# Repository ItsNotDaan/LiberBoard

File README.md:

# LiberBoard Electronics Learning Platform

## Vision

Our vision is to bridge the gap in electronics learning and project creation by providing well-documented and easy-to-access information points. We aim to empower individuals and educational institutions with the necessary tools and resources to ignite creativity and facilitate a seamless learning experience.

## Development

LiberBoard Electronics Learning Platform is developed with the user in mind, ensuring a high degree of modularity and flexibility. The platform consists of two main LiBo PCBs and several add-on boards, each serving a unique purpose and adding a different dimension to the learning process.

### Main Boards

1. **LiBo DUO**: A budget-friendly, two-layer PCB with hand-solderable components.
2. **LiBo QUAD**: A medium-budget, four-layer PCB solderable using a heat plate or oven.
3. **LiBo ESP32-S3 SOM**: A high speed system on module that can be connected to multiple add-on boards.

### Add-on Boards

1. **LiBo StarterBoard**: A board featuring a 16x2 LCD, 16 bit LEDs, an ADC sensor, and a temperature sensor.
2. **LiBo ArduinoBoard**: A board with an Arduino pinout, capable of communicating with Arduino Modules.
3. **LiBo DSPBoard**: An audio processing board with components for audio input/output, microphone, and speaker connectors.
4. **LiBo BaseBoard**: A programming stand/main board base station with easy access pinouts, BNC connectors, and status LEDs.

Each board is accompanied by exercises and code snippets to enable hands-on learning and practical understanding of electronics.

## Used Software and Products

All the LiBo PCB designs are created using the EDA software KiCad. The design files are open source and are available on GitHub, allowing users to recreate, modify, and order the PCBs. The platform also provides options for DIY PCB creation or ordering from the site.

## Conclusion

LiberBoard Electronics Learning Platform is a comprehensive solution for anyone looking to delve into the world of electronics. By providing well-documented, easy-to-use, and flexible resources, we hope to inspire a new generation of electronics enthusiasts and professionals.

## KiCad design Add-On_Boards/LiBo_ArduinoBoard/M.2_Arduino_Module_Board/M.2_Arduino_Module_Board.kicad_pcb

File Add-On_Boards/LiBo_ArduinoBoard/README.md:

# LiBo ArduinoBoard

The LiBo ArduinoBoard is an add-on board with Arduino pinout, enabling communication with Arduino modules.

## Features

- Arduino pinout
- M.2 interface
- Maximum component size: 0805
- Able to communicate with Arduino Modules
- Able to program main board using this board

## Exercises

- Blink
- SPI

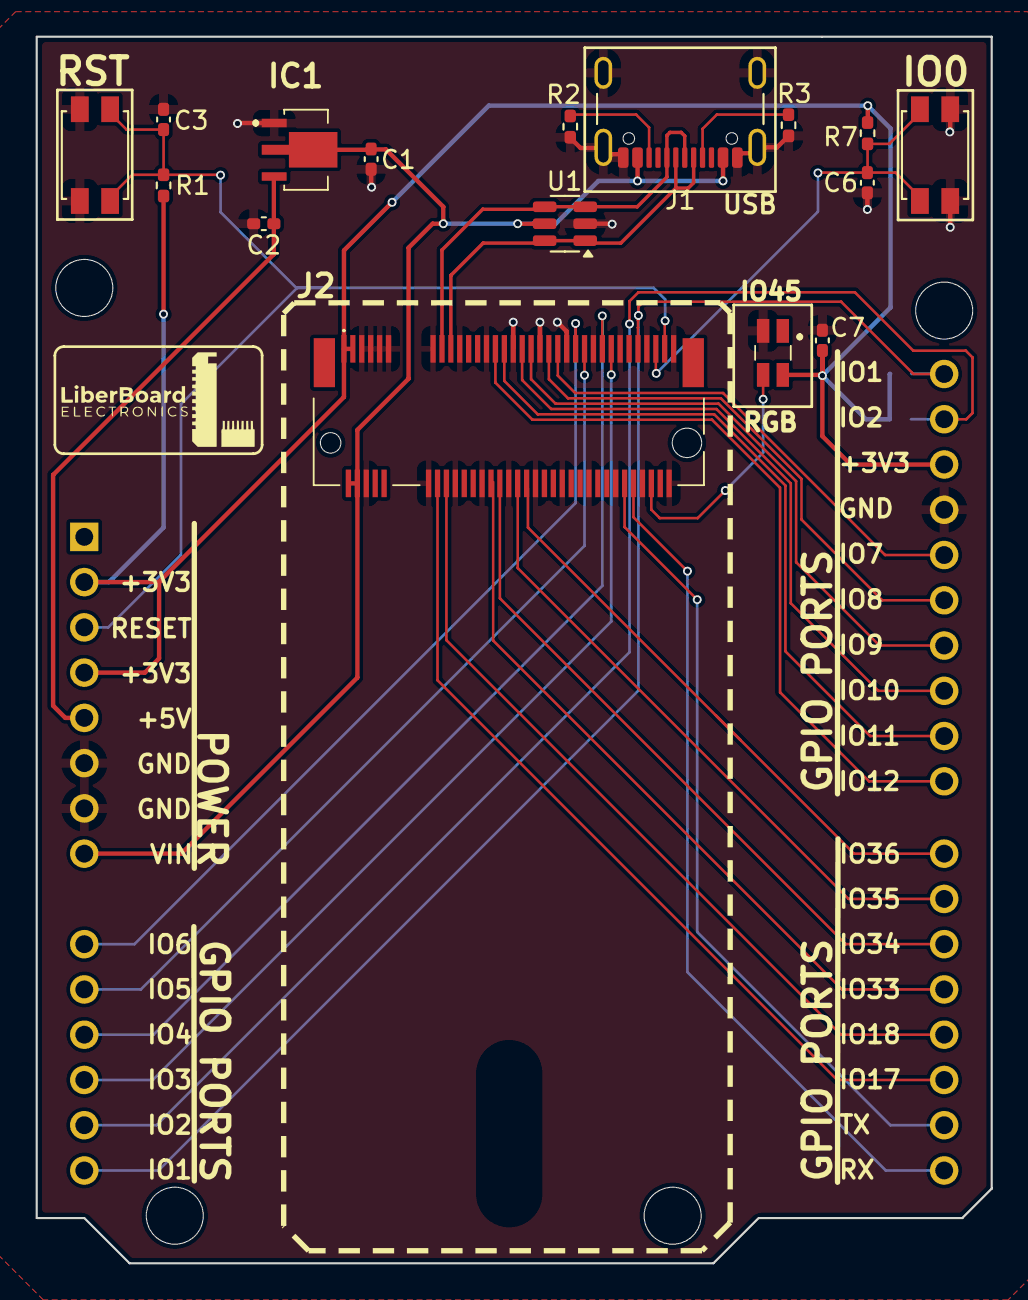
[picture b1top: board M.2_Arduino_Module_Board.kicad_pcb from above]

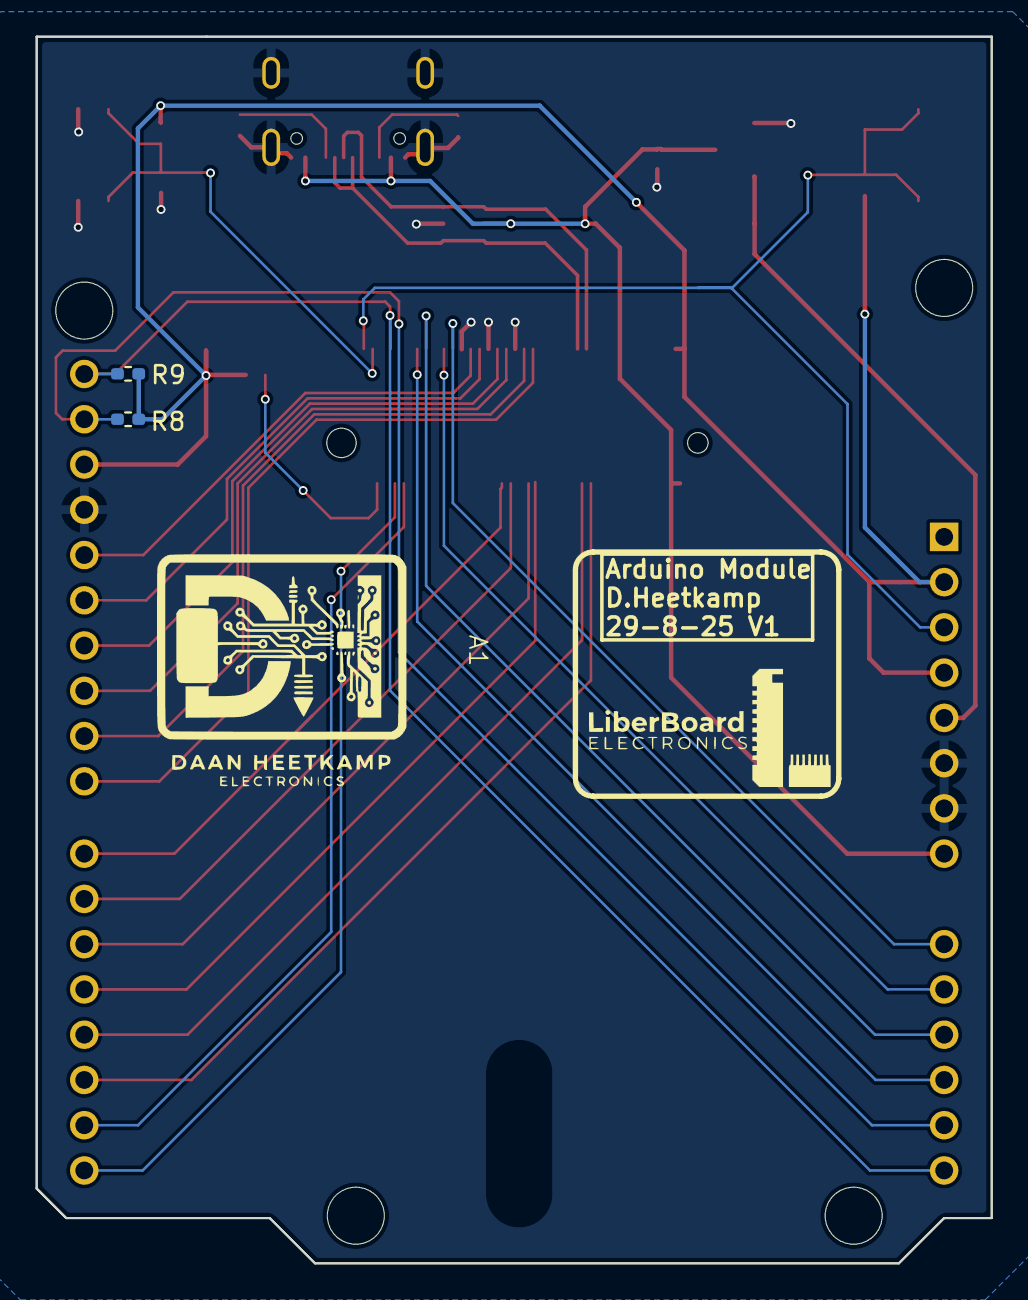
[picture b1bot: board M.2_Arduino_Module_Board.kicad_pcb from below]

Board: 2 copper layers, 53.6 x 68.8 mm, 19 parts (3 on the bottom side), 31 nets.

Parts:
A1: Arduino_Uno_Footprint
BOOT1: SW_BOOT; SW_SPST_EVQP2
C1, C2: 1u; C_0402_1005Metric_Pad0.74x0.62mm_HandSolder
C3, C6, C7: 100n; C_0402_1005Metric_Pad0.74x0.62mm_HandSolder
IC1: MCP1702T-5002E_MB; MCP1703T5002EMB
J1: USB_C_Receptacle_USB2.0; USB_C_Receptacle_GCT_USB4105-xx-A_16P_TopMnt_Horizontal
J2: 2199230-3; 21992303
LED1: WS2812C-2020; WS2812C2020
R1, R7: 10k; R_0402_1005Metric_Pad0.72x0.64mm_HandSolder
R2, R3, R8, R9: 5k1; R_0402_1005Metric_Pad0.72x0.64mm_HandSolder
RST1: SW_RST; SW_SPST_EVQP2
U1: USBLC6-2SC6; SOT-23-6

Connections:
+3V3: A1.2 (IOREF), A1.4 (3V3), A1.30 (AREF), C7.1, J2.1, J2.3, LED1.4 (VDD), R1.1, R7.1, R8.1, R9.1
+5V: A1.5 (+5V), C2.1, IC1.3 (VOUT)
/CHIP_BOOT: BOOT1.2, C6.1, J2.71, R7.2
/CHIP_PU: A1.3 (~RESET), C3.1, J2.73, R1.2, RST1.2
/GPIO1: A1.14 (SCL/A5), A1.32 (SCL/A5), J2.67, R9.2
/GPIO2: A1.13 (SDA/A4), A1.31 (SDA/A4), J2.65, R8.2
/GPIO3: A1.12 (A3), J2.61
/GPIO4: A1.11 (A2), J2.59
/GPIO5: A1.10 (A1), J2.55
/GPIO6: A1.9 (A0), J2.53
/GPIO7: A1.28 (D13), J2.49
/GPIO8: A1.27 (D12), J2.47
/GPIO9: A1.26 (D11), J2.43
/GPIO10: A1.25 (D10), J2.41
/GPIO11: A1.24 (D9), J2.37
/GPIO12: A1.23 (D8), J2.35
/GPIO17: A1.17 (D2), J2.22
/GPIO18: A1.18 (D3), J2.24
/GPIO33: A1.19 (D4), J2.34
/GPIO34: A1.20 (D5), J2.36
/GPIO35: A1.21 (D6), J2.40
/GPIO36: A1.22 (D7), J2.42
/GPIO45: J2.70, LED1.3 (DI)
/U0RXD: A1.15 (D0/RX), J2.66
/U0TXD: A1.16 (D1/TX), J2.64
/USB_CC1: J1.A5 (CC1), R3.1
/USB_CC2: J1.B5 (CC2), R2.1
/USB_D+: J1.A6 (D+), J1.B6 (D+), J2.23, U1.3 (I/O2), U1.4 (I/O2)
/USB_D-: J1.A7 (D-), J1.B7 (D-), J2.25, U1.1 (I/O1), U1.6 (I/O1)
Earth: A1.6 (GND), A1.7 (GND), A1.29 (GND), BOOT1.1, C1.2, C2.2, C3.2, C6.2, C7.2, IC1.1 (GND), J1.A1 (GND), J1.A12 (GND), J1.B1 (GND), J1.B12 (GND), J1.S1 (SHIELD), J2.5, J2.6, J2.7, J2.9, J2.11, J2.20, J2.21, J2.26, J2.27, J2.32, J2.33, J2.38, J2.39, J2.44, J2.45, J2.50, J2.51, J2.56, J2.57, J2.62, J2.63, J2.68, J2.69, J2.74, J2.75, LED1.2 (GND), R2.2, R3.2, RST1.1, U1.2 (GND)
VBUS: A1.8 (VIN), C1.1, IC1.2 (VIN_1), IC1.4 (VIN_2), J1.A4 (VBUS), J1.A9 (VBUS), J1.B4 (VBUS), J1.B9 (VBUS), J2.2, J2.4, U1.5 (VBUS)

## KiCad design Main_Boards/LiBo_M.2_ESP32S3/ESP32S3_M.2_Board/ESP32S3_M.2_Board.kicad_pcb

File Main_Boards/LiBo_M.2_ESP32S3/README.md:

## ESP32-S3, M.2 based System on Module (SOM)

This is my first KiCad project, developed over the last 2 months alongside my EPS project and work. 

## Versions:
### V1
The first version that was created. Soldered by hand. Did not boot properly. 

### V2
The second version got a redesign of the main ESP32 S3 connections. This time hopefully with the correct connections. 
Some bootpins were removed to change to a more usable setup. The board has also been ordered with assembly to make sure the soldering is correct. 

### Main Components

- **CPU:** ESP32-S3R8
- **Flash:** W25Q16JVUXIQ (16MBIT)
- **Crystals:** 40MHz and 32.768KHz (HSE/LSE)
- **Power/Flashing/Debugging:** USB-C
- **Buck Converter:** TLV62568DBV
- **Buttons:** Two buttons for RESET and BOOT
- **Antenna:** Antenna with PI filter
- **PCB:** 4-layer PCB (Top, GND, VCC, Bottom), internal planes are hidden

All these components are included on a M.2-B-Key footprint. 

## JLCPCB Ordering Details

- **Base Material:** FR-4
- **Layers:** 4
- **Dimension:** 70.97 mm × 70 mm
- **PCB Thickness:** 0.8 mm
- **Specify Stackup:** yes — JLC04081H-7628
- **Impedance Control:** No requirement
- **Material Type:** FR4 TG135
- **Via Covering:** Plugged
- **Surface Finish:** ENIG — Gold Thickness: 1U"
- **Outer Copper Weight:** 1 oz
- **Inner Copper Weight:** 0.5 oz
- **Gold Fingers:** Yes
- **Beveling:** 45°
- **Mark on PCB:** 2D barcode (Serial Number)
- **Min via hole size/diameter:** 0.3 mm / (0.4 / 0.45 mm)
- **Appearance Quality:** IPC Class 2 Standard
- **Silkscreen Technology:** Ink-jet/Screen Printing Silkscreen
- **Package Box:** With JLCPCB logo
- **Board Outline Tolerance:** ±0.2 mm (Regular)

### Notes
- **Layer Sequence:** Top / GND / VCC / Bottom (from design)
- **NOTE:** If a detail is not shown it means the standard is used. 
 
### Inspiration

The idea originated from a desire to create a more complex and smaller PCB that incorporates an expensive CPU. This CPU should be versatile enough to be used on different projects. After watching a video from Phil's Lab, I learned that M.2 was a great alternative to the mostly used header pin setup. 

### Future Plans

The ESP32-S3 is not high-end or anything special, but I plan to quickly redesign this board using the newly announced ESP32-P4. It is a really interesting and high-speed CPU based on the RISC-V architecture and I'm excited to start creating some (DSP) code with it. 

I have ordered the components and the PCB to start experimenting with it.

https://www.linkedin.com/in/daan-heetkamp/

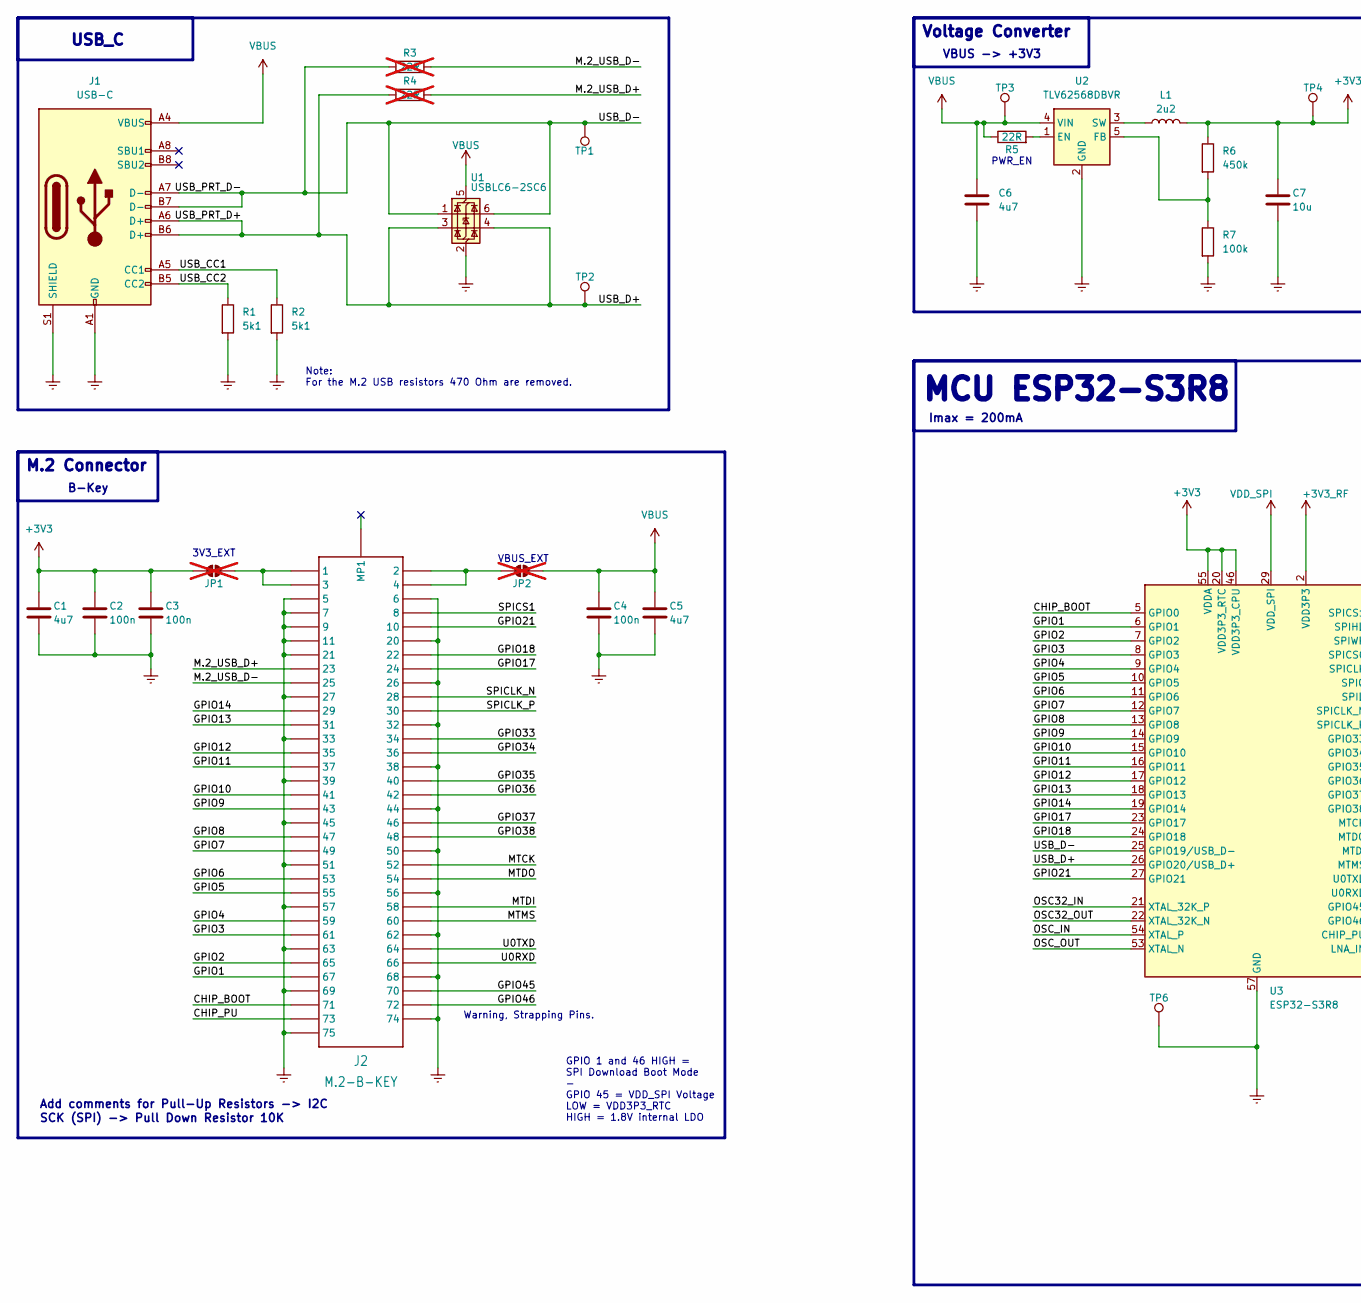
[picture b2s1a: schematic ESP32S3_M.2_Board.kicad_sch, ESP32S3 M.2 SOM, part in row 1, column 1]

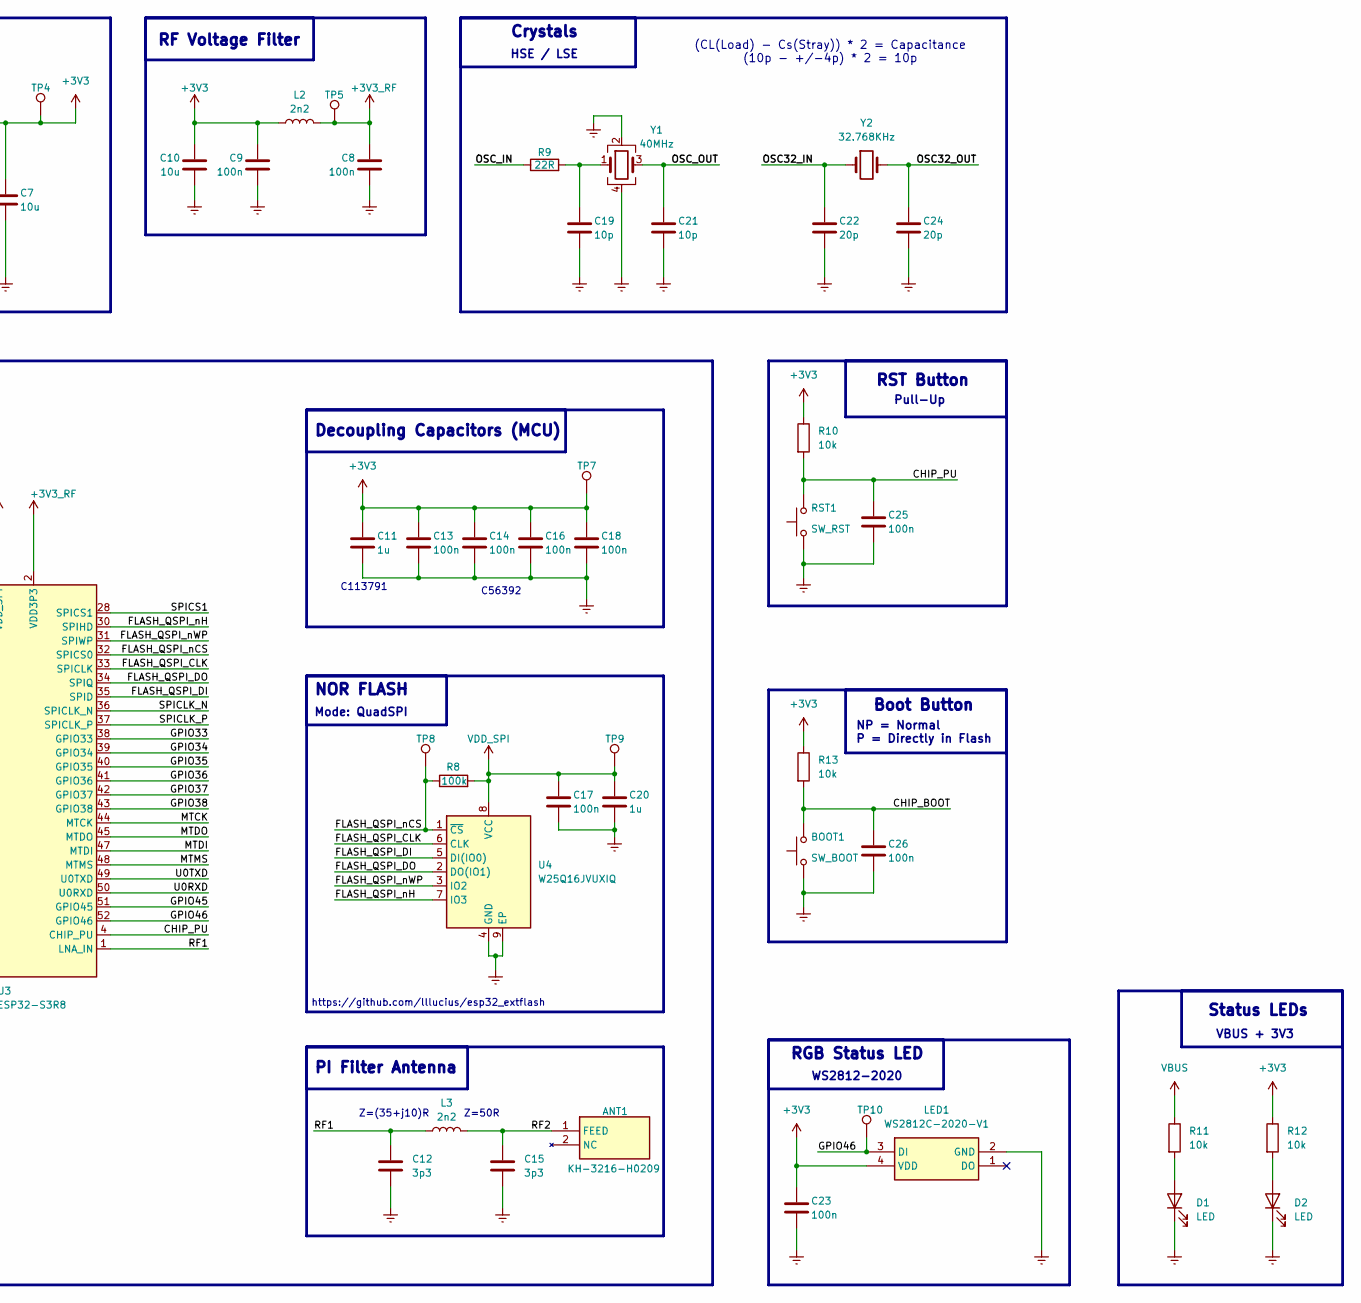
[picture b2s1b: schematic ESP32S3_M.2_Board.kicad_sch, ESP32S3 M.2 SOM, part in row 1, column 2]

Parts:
ANT1: KH-3216-H0209; ANTC3216X140N; Manufacturer_Part_Number KH-3216-H0209; LCSC PART # C2925417
BOOT1: SW_BOOT; SW_SPST_EVQP2; Manufacturer_Part_Number EVQP2P02W; LCSC PART # C512395
C1, C5, C6: 4u7; C_0402_1005Metric_Pad0.74x0.62mm_HandSolder; Manufacturer_Part_Number GRM155R60J475ME47D; LCSC PART # C82453
C2, C3, C4, C8, C9, C13, C14, C16, C17, C18, C23, C25, C26: 100n; C_0402_1005Metric_Pad0.74x0.62mm_HandSolder; Manufacturer_Part_Number C1005X5R1E104KT000E; LCSC PART # C361203
C7, C10: 10u; C_0402_1005Metric_Pad0.74x0.62mm_HandSolder; Manufacturer_Part_Number 0402X106M100CT; LCSC PART # C2992625
C11, C20: 1u; C_0402_1005Metric_Pad0.74x0.62mm_HandSolder; Manufacturer_Part_Number CC0402MRX5R6BB105; LCSC PART # C113791
C12, C15: 3p3; C_0603_1608Metric_Pad1.08x0.95mm_HandSolder; Manufacturer_Part_Number 0603CG3R3C500NT; LCSC PART # C1660
C19, C21: 10p; C_0402_1005Metric_Pad0.74x0.62mm_HandSolder; Manufacturer_Part_Number C1005NP0100JGTS; LCSC PART # C258501
C22, C24: 20p; C_0402_1005Metric_Pad0.74x0.62mm_HandSolder; Manufacturer_Part_Number CC0402JRNPO9BN200; LCSC PART # C107000
D1, D2: LED; LED_0402_1005Metric_Pad0.77x0.64mm_HandSolder; Manufacturer_Part_Number XL-1005SURC; LCSC PART # C25503345
J1: USB-C; USB_C_Receptacle_GCT_USB4105-xx-A_16P_TopMnt_Horizontal; Manufacturer_Part_Number MC-311D; LCSC PART # C136423
J2: M.2-B-KEY
JP1: 3V3_M2; R_0201_0603Metric; not fitted
JP2: VBUS_M2; R_0201_0603Metric; not fitted
L1: 2u2; L_Wurth_WE-LQSH-4020; Manufacturer_Part_Number SMNR4020-2.2UH; LCSC PART # C135262
L2, L3: 2n2; L_0603_1608Metric_Pad1.05x0.95mm_HandSolder; Manufacturer_Part_Number SDCL1608C2N2STDF; LCSC PART # C29682
LED1: WS2812C-2020-V1; WS2812C2020; Manufacturer_Part_Number WS2812C-2020; LCSC PART # C2976072
R1, R2: 5k1; R_0402_1005Metric_Pad0.72x0.64mm_HandSolder; Manufacturer_Part_Number RC0402JR-075K1L; LCSC PART # C105873
R3, R4: 22R; R_0201_0603Metric; not fitted
R5, R9: 22R; R_0402_1005Metric_Pad0.72x0.64mm_HandSolder; Manufacturer_Part_Number ERJ2RKF22R0X; LCSC PART # C413049
R6: 450k; R_0402_1005Metric_Pad0.72x0.64mm_HandSolder; Manufacturer_Part_Number FRC0402F4503TS; LCSC PART # C5159688
R7, R8: 100k; R_0402_1005Metric_Pad0.72x0.64mm_HandSolder; Manufacturer_Part_Number RT0402CRE07100KL; LCSC PART # C705662
R10, R11, R12, R13: 10k; R_0402_1005Metric_Pad0.72x0.64mm_HandSolder; Manufacturer_Part_Number WR04X1002FTL; LCSC PART # C163810
RST1: SW_RST; SW_SPST_EVQP2; Manufacturer_Part_Number EVQP2P02W; LCSC PART # C512395
TP1, TP2, TP3, TP4, TP5, TP6, TP7, TP8, TP9, TP10: TestPoint; TestPoint_Pad_D1.0mm
U1: USBLC6-2SC6; SOT-23-6; Manufacturer_Part_Number USBLC6-2SC6; LCSC PART # C2827654
U2: TLV62568DBVR; SOT-23-5; Manufacturer_Part_Number TLV62568DBVR; LCSC PART # C163219
U3: ESP32-S3R8; QFN-56-1EP_7x7mm_P0.4mm_EP4x4mm; Manufacturer_Part_Number ESP32-S3R8; LCSC PART # C2913194
U4: W25Q16JVUXIQ; USON-8-2X3_P0.6mm; Manufacturer_Part_Number W25Q16JVUXIQ; LCSC PART # C2843335
Y1: 40MHz; Crystal_SMD_3225-4Pin_3.2x2.5mm; Manufacturer_Part_Number X252040MMB4SI; LCSC PART # C2885592
Y2: 32.768KHz; Crystal_SMD_3215-2Pin_3.2x1.5mm; Manufacturer_Part_Number DST310S 32.768KHz; LCSC PART # C93232

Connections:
+3V3: C1.1, C2.1, C3.1, C7.1, C9.1, C10.1, C11.1, C13.1, C14.1, C16.1, C18.1, C23.1, JP1.2 (B), L1.2, L2.2, LED1.4 (VDD), R6.1, R10.1, R12.1, R13.1, TP4.1, TP7.1, U3.20 (VDD3P3_RTC), U3.46 (VDD3P3_CPU), U3.55 (VDDA), U3.56 (VDDA)
+3V3_RF: C8.1, L2.1, TP5.1, U3.2 (VDD3P3), U3.3 (VDD3P3)
/CHIP_BOOT: BOOT1.2, C26.1, J2.P$71 (71), R13.2, U3.5 (GPIO0)
/CHIP_PU: C25.1, J2.P$73 (73), R10.2, RST1.2, U3.4 (CHIP_PU)
/FLASH_QSPI_CLK: U3.33 (SPICLK), U4.6 (CLK)
/FLASH_QSPI_DI: U3.35 (SPID), U4.5 (DI(IO0))
/FLASH_QSPI_DO: U3.34 (SPIQ), U4.2 (DO(IO1))
/FLASH_QSPI_nCS: R8.1, TP8.1, U3.32 (SPICS0), U4.1 (~CS)
/FLASH_QSPI_nH: U3.30 (SPIHD), U4.7 (IO3)
/FLASH_QSPI_nWP: U3.31 (SPIWP), U4.3 (IO2)
/GPIO1: J2.P$67 (67), U3.6 (GPIO1)
/GPIO2: J2.P$65 (65), U3.7 (GPIO2)
/GPIO3: J2.P$61 (61), U3.8 (GPIO3)
/GPIO4: J2.P$59 (59), U3.9 (GPIO4)
/GPIO5: J2.P$55 (55), U3.10 (GPIO5)
/GPIO6: J2.P$53 (53), U3.11 (GPIO6)
/GPIO7: J2.P$49 (49), U3.12 (GPIO7)
/GPIO8: J2.P$47 (47), U3.13 (GPIO8)
/GPIO9: J2.P$43 (43), U3.14 (GPIO9)
/GPIO10: J2.P$41 (41), U3.15 (GPIO10)
/GPIO11: J2.P$37 (37), U3.16 (GPIO11)
/GPIO12: J2.P$35 (35), U3.17 (GPIO12)
/GPIO13: J2.P$31 (31), U3.18 (GPIO13)
/GPIO14: J2.P$29 (29), U3.19 (GPIO14)
/GPIO17: J2.P$24 (24), U3.23 (GPIO17)
/GPIO18: J2.P$22 (22), U3.24 (GPIO18)
/GPIO21: J2.P$10 (10), U3.27 (GPIO21)
/GPIO33: J2.P$34 (34), U3.38 (GPIO33)
/GPIO34: J2.P$36 (36), U3.39 (GPIO34)
/GPIO35: J2.P$40 (40), U3.40 (GPIO35)
/GPIO36: J2.P$42 (42), U3.41 (GPIO36)
/GPIO37: J2.P$46 (46), U3.42 (GPIO37)
/GPIO38: J2.P$48 (48), U3.43 (GPIO38)
/GPIO45: J2.P$70 (70), U3.51 (GPIO45)
/GPIO46: J2.P$72 (72), LED1.3 (DI), TP10.1, U3.52 (GPIO46)
/M.2_USB_D+: J2.P$23 (23), R4.2
/M.2_USB_D-: J2.P$25 (25), R3.2
/MTCK: J2.P$52 (52), U3.44 (MTCK)
/MTDI: J2.P$58 (58), U3.47 (MTDI)
/MTDO: J2.P$54 (54), U3.45 (MTDO)
/MTMS: J2.P$60 (60), U3.48 (MTMS)
/OSC32_IN: C22.1, U3.21 (XTAL_32K_P), Y2.1
/OSC32_OUT: C24.1, U3.22 (XTAL_32K_N), Y2.2
/OSC_IN: R9.1, U3.54 (XTAL_P)
/OSC_OUT: C21.1, U3.53 (XTAL_N), Y1.3
/RF1: C12.1, L3.1, U3.1 (LNA_IN)
/RF2: ANT1.1 (FEED), C15.1, L3.2
/SPICLK_N: J2.P$28 (28), U3.36 (SPICLK_N)
/SPICLK_P: J2.P$30 (30), U3.37 (SPICLK_P)
/SPICS1: J2.P$8 (8), U3.28 (SPICS1)
/U0RXD: J2.P$66 (66), U3.50 (U0RXD)
/U0TXD: J2.P$64 (64), U3.49 (U0TXD)
/USB_CC1: J1.A5 (CC1), R2.1
/USB_CC2: J1.B5 (CC2), R1.1
/USB_D+: J1.A6 (D+), J1.B6 (D+), R4.1, TP2.1, U1.3 (I/O2), U1.4 (I/O2), U3.26 (GPIO20/USB_D+)
/USB_D-: J1.A7 (D-), J1.B7 (D-), R3.1, TP1.1, U1.1 (I/O1), U1.6 (I/O1), U3.25 (GPIO19/USB_D-)
Earth: BOOT1.1, C1.2, C2.2, C3.2, C4.2, C5.2, C6.2, C7.2, C8.2, C9.2, C10.2, C11.2, C12.2, C13.2, C14.2, C15.2, C16.2, C17.2, C18.2, C19.2, C20.2, C21.2, C22.2, C23.2, C24.2, C25.2, C26.2, D1.1 (K), D2.1 (K), J1.A1 (GND), J1.A12 (GND), J1.B1 (GND), J1.B12 (GND), J1.S1 (SHIELD), J2.MOUNTING-HOLE (MP1), J2.P$5 (5), J2.P$6 (6), J2.P$7 (7), J2.P$9 (9), J2.P$11 (11), J2.P$20 (20), J2.P$21 (21), J2.P$26 (26), J2.P$27 (27), J2.P$32 (32), J2.P$33 (33), J2.P$38 (38), J2.P$39 (39), J2.P$44 (44), J2.P$45 (45), J2.P$50 (50), J2.P$51 (51), J2.P$56 (56), J2.P$57 (57), J2.P$62 (62), J2.P$63 (63), J2.P$68 (68), J2.P$69 (69), J2.P$74 (74), J2.P$75 (75), LED1.2 (GND), R1.2, R2.2, R7.2, RST1.1, TP6.1, U1.2 (GND), U2.2 (GND), U3.57 (GND), U4.4 (GND), U4.9 (EP), Y1.2, Y1.4
unnamed: C19.1, R9.2, Y1.1
unnamed: D1.2 (A), R11.2
unnamed: D2.2 (A), R12.2
unnamed: J2.P$1 (1), J2.P$3 (3), JP1.1 (A)
unnamed: J2.P$2 (2), J2.P$4 (4), JP2.2 (B)
unnamed: R5.2, U2.1 (EN)
unnamed: R6.2, R7.1, U2.5 (FB)
unnamed: L1.1, U2.3 (SW)
VBUS: C4.1, C5.1, C6.1, J1.A4 (VBUS), J1.A9 (VBUS), J1.B4 (VBUS), J1.B9 (VBUS), JP2.1 (A), R5.1, R11.1, TP3.1, U1.5 (VBUS), U2.4 (VIN)
VDD_SPI: C17.1, C20.1, R8.2, TP9.1, U3.29 (VDD_SPI), U4.8 (VCC)

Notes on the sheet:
RGB Status LED
VBUS_EXT
3V3_EXT
VBUS + 3V3
Crystals
B-Key
NP = Normal P = Directly in Flash
HSE / LSE
Note: For the M.2 USB resistors 470 Ohm are removed.
Add comments for Pull-Up Resistors -> I2C
Voltage Converter
MCU ESP32-S3R8
RF Voltage Filter
Mode: QuadSPI
NOR FLASH
USB_C
C113791
SCK (SPI) -> Pull Down Resistor 10K
M.2 Connector
RST Button
WS2812-2020
PWR_EN
Decoupling Capacitors (MCU)
Boot Button
C56392
Status LEDs
Warning, Strapping Pins.
VBUS -> +3V3
GPIO 1 and 46 HIGH = SPI Download Boot Mode - GPIO 45 = VDD_SPI Voltage LOW = VDD3P3_RTC HIGH = 1.8V internal LDO
Z=(35+j10)R
PI Filter Antenna
(CL(Load) - Cs(Stray)) * 2 = Capacitance (10p - +/-4p) * 2 = 10p
Imax = 200mA
Z=50R
https://github.com/lllucius/esp32_extflash
Pull-Up

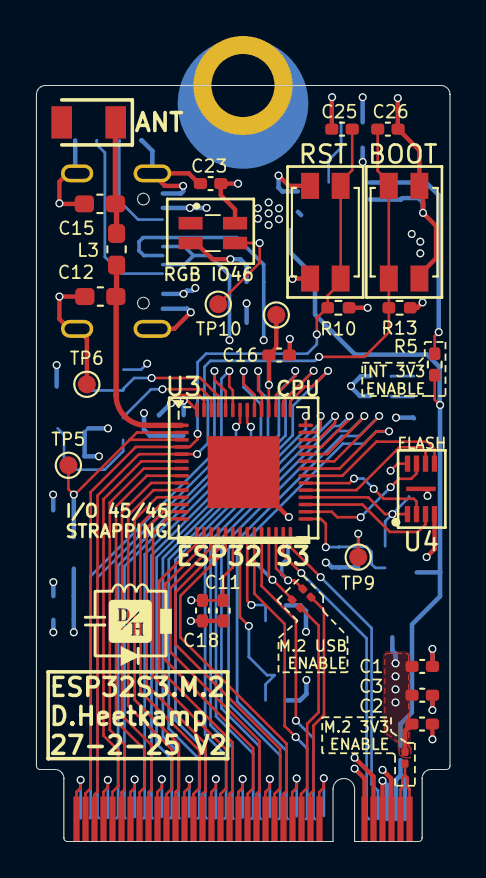
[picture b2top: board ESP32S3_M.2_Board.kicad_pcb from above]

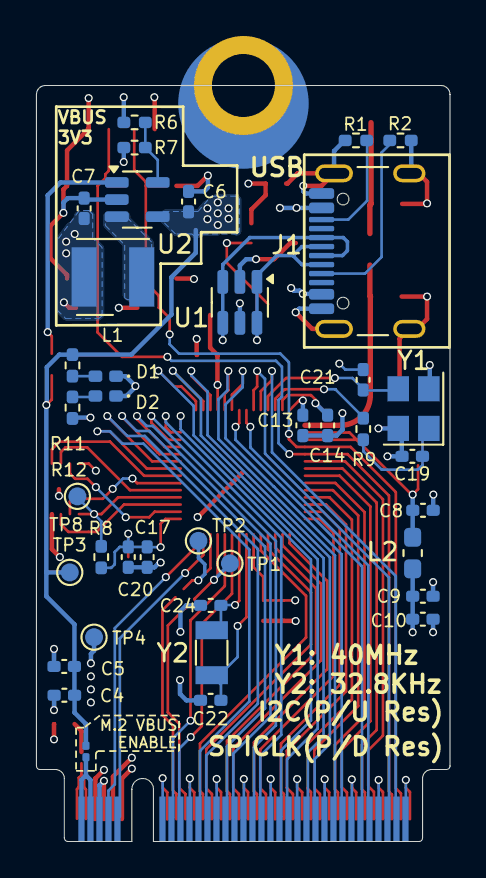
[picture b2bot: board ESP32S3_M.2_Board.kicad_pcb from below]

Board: 4 copper layers, 23.0 x 42.0 mm, 68 parts (38 on the bottom side), 67 nets.

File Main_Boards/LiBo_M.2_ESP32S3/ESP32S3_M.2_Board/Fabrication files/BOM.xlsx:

Comment | Designator | Footprint | JLCPCB PART #
32.768KHz | Y2 | Crystal:Crystal_SMD_3215-2Pin_3.2x1.5mm | C93232
40MHz | Y1 | Crystal:Crystal_SMD_3225-4Pin_3.2x2.5mm | C2885592
W25Q16JVUXIQ | U4 | PCB_Lib_DaanHeetkamp_KiCad:USON-8-2X3_P0.6mm | C2843335
ESP32-S3R8 | U3 | Package_DFN_QFN:QFN-56-1EP_7x7mm_P0.4mm_EP4x4mm | C2913194
TLV62568DBVR | U2 | Package_TO_SOT_SMD:SOT-23-5 | C163219
USBLC6-2SC6 | U1 | Package_TO_SOT_SMD:SOT-23-6 | C2827654
TestPoint | TP1,TP2,TP3,TP4,TP5,TP6,TP7,TP8,TP9,TP10 | TestPoint:TestPoint_Pad_D1.0mm
SW_RST | RST1 | Button_Switch_SMD:SW_SPST_EVQP2 | C512395
100k | R7,R8 | Resistor_SMD:R_0402_1005Metric_Pad0.72x0.64mm_HandSolder | C705662
22R | R5,R9 | Resistor_SMD:R_0402_1005Metric_Pad0.72x0.64mm_HandSolder | C413049
10k | R10,R11,R12,R13 | Resistor_SMD:R_0402_1005Metric_Pad0.72x0.64mm_HandSolder | C163810
5k1 | R1,R2 | Resistor_SMD:R_0402_1005Metric_Pad0.72x0.64mm_HandSolder | C105873
450k | R6 | Resistor_SMD:R_0402_1005Metric_Pad0.72x0.64mm_HandSolder | C5159688
WS2812C-2020-V1 | LED1 | PCB_Lib_DaanHeetkamp_KiCad:WS2812C2020 | C2976072
2n2 | L2,L3 | Inductor_SMD:L_0603_1608Metric_Pad1.05x0.95mm_HandSolder | C29682
2u2 | L1 | Inductor_SMD_Wurth:L_Wurth_WE-LQSH-4020 | C135262
M.2-B-KEY | J2 | M.2-Card-Footprints:M.2-B-KEY
USB-C | J1 | Connector_USB:USB_C_Receptacle_GCT_USB4105-xx-A_16P_TopMnt_Horizontal | C136423
LED | D1,D2 | LED_SMD:LED_0402_1005Metric_Pad0.77x0.64mm_HandSolder | C25503345
10u | C7,C10 | Capacitor_SMD:C_0402_1005Metric_Pad0.74x0.62mm_HandSolder | C2992625
20p | C22,C24 | Capacitor_SMD:C_0402_1005Metric_Pad0.74x0.62mm_HandSolder | C107000
100n | C2,C3,C4,C8,C9,C13,C14,C16,C17,C18,C23,C25,C26 | Capacitor_SMD:C_0402_1005Metric_Pad0.74x0.62mm_HandSolder | C361203
10p | C19,C21 | Capacitor_SMD:C_0402_1005Metric_Pad0.74x0.62mm_HandSolder | C258501
3p3 | C12,C15 | Capacitor_SMD:C_0603_1608Metric_Pad1.08x0.95mm_HandSolder | C1660
1u | C11,C20 | Capacitor_SMD:C_0402_1005Metric_Pad0.74x0.62mm_HandSolder | C113791
4u7 | C1,C5,C6 | Capacitor_SMD:C_0402_1005Metric_Pad0.74x0.62mm_HandSolder | C82453
SW_BOOT | BOOT1 | Button_Switch_SMD:SW_SPST_EVQP2 | C512395
KH-3216-H0209 | ANT1 | PCB_Lib_DaanHeetkamp_KiCad:ANTC3216X140N | C2925417

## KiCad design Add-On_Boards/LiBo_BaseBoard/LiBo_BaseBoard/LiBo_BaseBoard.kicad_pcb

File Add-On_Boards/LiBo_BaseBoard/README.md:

# LiBo BaseBoard

The LiBo BaseBoard serves as a programming stand and base station for the main boards.

## Features

- Slide in the PCB vertically
- M.2 interface
- Maximum component size: 0805
- Some pinouts at the front for easy access and fast testing
- Two BNC connectors
- Status LEDs

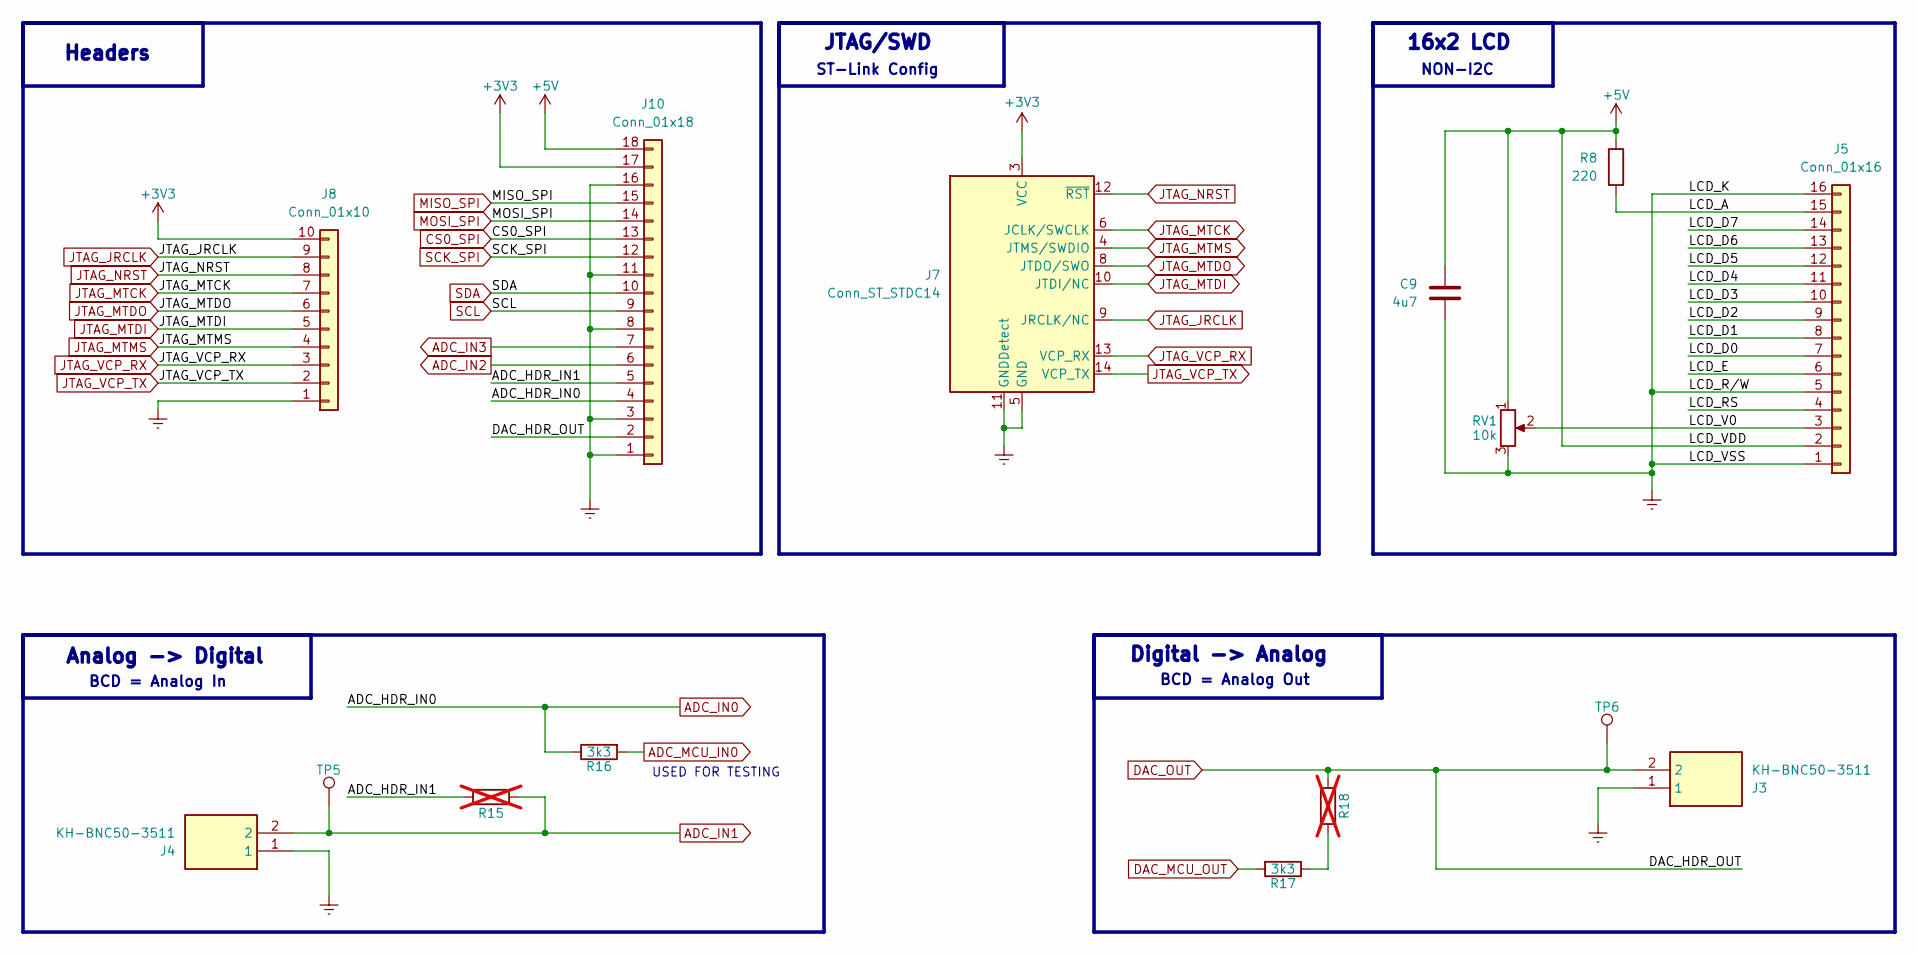
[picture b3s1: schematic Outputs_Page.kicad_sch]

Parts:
C9: 4u7; C_0805_2012Metric_Pad1.18x1.45mm_HandSolder
J3, J4: KH-BNC50-3511; KHBNC503511; Manufacturer_Part_Number KH-BNC50-3511
J5: Conn_01x16; PinHeader_1x16_P2.54mm_Vertical
J7: Conn_ST_STDC14; PinHeader_2x07_P1.27mm_Vertical
J8: Conn_01x10; PinHeader_1x10_P2.54mm_Vertical
J10: Conn_01x18; PinHeader_1x18_P2.54mm_Horizontal
R8: 220; R_0805_2012Metric_Pad1.20x1.40mm_HandSolder
R15, R18: 10k; R_0805_2012Metric_Pad1.20x1.40mm_HandSolder; not fitted
R16, R17: 3k3; R_0805_2012Metric_Pad1.20x1.40mm_HandSolder
RV1: 10k; Potentiometer_Bourns_3296W_Vertical
TP5, TP6: TestPoint; TestPoint_Pad_D1.0mm

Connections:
+3V3: J7.3 (VCC), J8.10, J10.17; also elsewhere on the board
+5V: C9.1, J5.2, J10.18, R8.1, RV1.1; also elsewhere on the board
/OUTPUTS/ADC_HDR_IN1: J10.5, R15.2
/OUTPUTS/LCD_A: J5.15, R8.2
/OUTPUTS/LCD_D0: J5.7
/OUTPUTS/LCD_D1: J5.8
/OUTPUTS/LCD_D2: J5.9
/OUTPUTS/LCD_D3: J5.10
/OUTPUTS/LCD_D4: J5.11
/OUTPUTS/LCD_D5: J5.12
/OUTPUTS/LCD_D6: J5.13
/OUTPUTS/LCD_D7: J5.14
/OUTPUTS/LCD_E: J5.6
/OUTPUTS/LCD_RS: J5.4
/OUTPUTS/LCD_V0: J5.3, RV1.2
ADC_IN0: J10.4, R16.1; also elsewhere on the board
ADC_IN1: J4.2, R15.1, TP5.1; also elsewhere on the board
ADC_IN2: J10.6; also elsewhere on the board
ADC_IN3: J10.7; also elsewhere on the board
ADC_MCU_IN0: R16.2; also elsewhere on the board
CS0_SPI: J10.13; also elsewhere on the board
DAC_MCU_OUT: R17.2; also elsewhere on the board
DAC_OUT: J3.2, J10.2, R18.2, TP6.1; also elsewhere on the board
Earth: C9.2, J3.1, J4.1, J5.1, J5.5, J5.16, J7.5 (GND), J7.7 (GND), J7.11 (GNDDetect), J8.1, J10.1, J10.3, J10.8, J10.11, J10.16, RV1.3; also elsewhere on the board
JTAG_JRCLK: J7.9 (JRCLK/NC), J8.9; also elsewhere on the board
JTAG_MTCK: J7.6 (JCLK/SWCLK), J8.7; also elsewhere on the board
JTAG_MTDI: J7.10 (JTDI/NC), J8.5; also elsewhere on the board
JTAG_MTDO: J7.8 (JTDO/SWO), J8.6; also elsewhere on the board
JTAG_MTMS: J7.4 (JTMS/SWDIO), J8.4; also elsewhere on the board
JTAG_NRST: J7.12 (~RST), J8.8; also elsewhere on the board
JTAG_VCP_RX: J7.13 (VCP_RX), J8.3; also elsewhere on the board
JTAG_VCP_TX: J7.14 (VCP_TX), J8.2; also elsewhere on the board
MISO_SPI: J10.15; also elsewhere on the board
MOSI_SPI: J10.14; also elsewhere on the board
unnamed: R17.1, R18.1
SCK_SPI: J10.12; also elsewhere on the board
SCL: J10.9; also elsewhere on the board
SDA: J10.10; also elsewhere on the board

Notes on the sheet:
ST-Link Config
JTAG/SWD
Analog -> Digital
BCD = Analog In
USED FOR TESTING
Headers
Digital -> Analog
NON-I2C
16x2 LCD
BCD = Analog Out

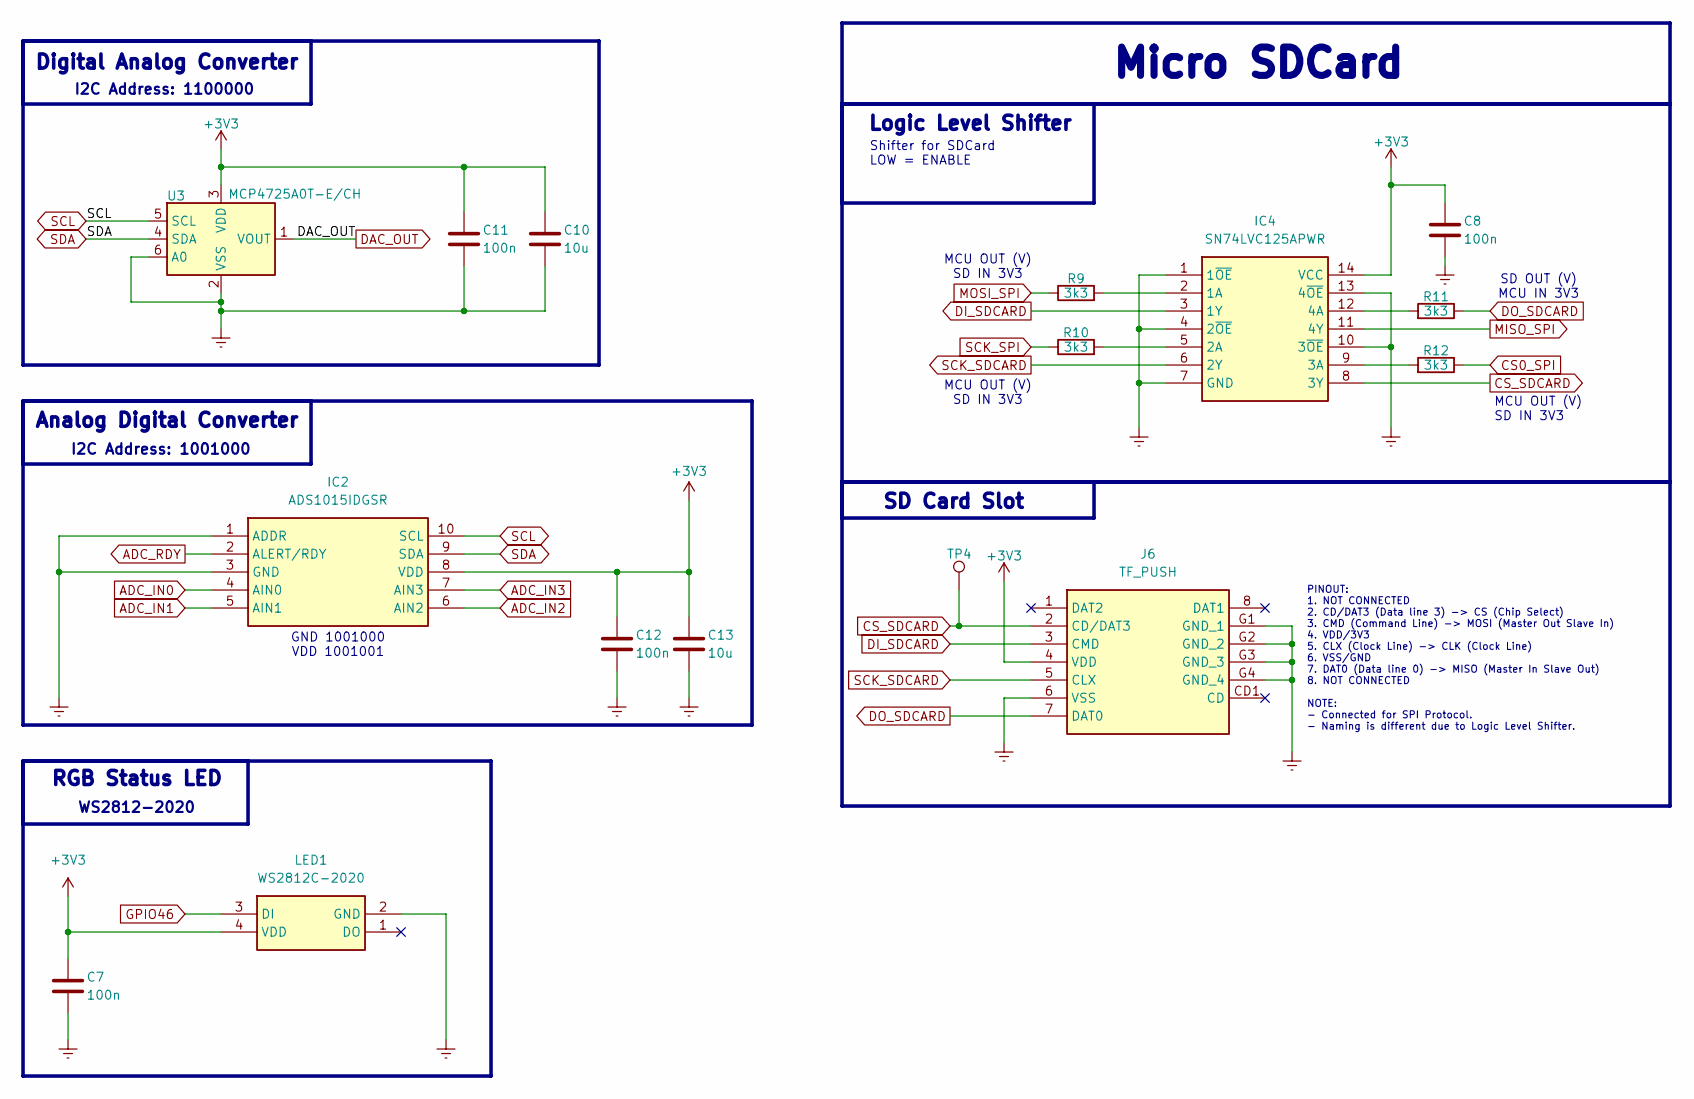
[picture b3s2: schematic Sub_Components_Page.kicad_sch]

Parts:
C7, C8, C11, C12: 100n; C_0805_2012Metric_Pad1.18x1.45mm_HandSolder
C10, C13: 10u; C_0805_2012Metric_Pad1.18x1.45mm_HandSolder
IC2: ADS1015IDGSR; SOP50P490X110-10N; Manufacturer_Part_Number ADS1015IDGSR
IC4: SN74LVC125APWR; Manufacturer_Part_Number SN74LVC125APWR
J6: TF_PUSH; TFPUSH; Manufacturer_Part_Number TF PUSH
LED1: WS2812C-2020; WS2812C2020; Manufacturer_Part_Number WS2812C-2020
R9, R10, R11, R12: 3k3; R_0805_2012Metric_Pad1.20x1.40mm_HandSolder
TP4: TestPoint; TestPoint_Pad_D1.0mm
U3: MCP4725A0T-E/CH; SOT-23-6

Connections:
+3V3: C7.1, C8.1, C10.1, C11.1, C12.1, C13.1, IC2.8 (VDD), IC4.14 (VCC), J6.4 (VDD), LED1.4 (VDD), U3.3 (VDD); also elsewhere on the board
ADC_IN0: IC2.4 (AIN0); also elsewhere on the board
ADC_IN1: IC2.5 (AIN1); also elsewhere on the board
ADC_IN2: IC2.6 (AIN2); also elsewhere on the board
ADC_IN3: IC2.7 (AIN3); also elsewhere on the board
ADC_RDY: IC2.2 (ALERT/RDY); also elsewhere on the board
CS0_SPI: R12.1; also elsewhere on the board
CS_SDCARD: IC4.8 (3Y), J6.2 (CD/DAT3), TP4.1
DAC_OUT: U3.1 (VOUT); also elsewhere on the board
DI_SDCARD: IC4.3 (1Y), J6.3 (CMD)
DO_SDCARD: J6.7 (DAT0), R11.1
Earth: C7.2, C8.2, C10.2, C11.2, C12.2, C13.2, IC2.1 (ADDR), IC2.3 (GND), IC4.1 (1~OE), IC4.4 (2~OE), IC4.7 (GND), IC4.10 (3~OE), IC4.13 (4~OE), J6.6 (VSS), J6.G1 (GND_1), J6.G2 (GND_2), J6.G3 (GND_3), J6.G4 (GND_4), LED1.2 (GND), U3.2 (VSS), U3.6 (A0); also elsewhere on the board
GPIO46: LED1.3 (DI)
MISO_SPI: IC4.11 (4Y); also elsewhere on the board
MOSI_SPI: R9.1; also elsewhere on the board
unnamed: IC4.2 (1A), R9.2
unnamed: IC4.5 (2A), R10.2
unnamed: IC4.9 (3A), R12.2
unnamed: IC4.12 (4A), R11.2
SCK_SDCARD: IC4.6 (2Y), J6.5 (CLX)
SCK_SPI: R10.1; also elsewhere on the board
SCL: IC2.10 (SCL), U3.5 (SCL); also elsewhere on the board
SDA: IC2.9 (SDA), U3.4 (SDA); also elsewhere on the board

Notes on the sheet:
Digital Analog Converter
MCU OUT (V) SD IN 3V3
WS2812-2020
Analog Digital Converter
I2C Address: 1001000
I2C Address: 1100000
SD OUT (V) MCU IN 3V3
Shifter for SDCard LOW = ENABLE
SD Card Slot
GND 1001000 VDD 1001001
RGB Status LED
Micro SDCard
Logic Level Shifter
PINOUT: 1. NOT CONNECTED 2. CD/DAT3 (Data line 3) -> CS (Chip Select) 3. CMD (Command Line) -> MOSI (Master Out Slave In) 4. VDD/3V3 5. CLX (Clock Line) -> CLK (Clock Line) 6. VSS/GND 7. DAT0 (Data line 0) -> MISO (Master In Slave Out) 8. NOT CONNECTED NOTE: - Connected for SPI Protocol. - Naming i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
